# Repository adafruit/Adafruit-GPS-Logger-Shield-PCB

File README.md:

## Adafruit GPS Logger Shield PCB
<a href="http://www.adafruit.com/products/1272"><br/>
Click here to purchase one from the Adafruit shop</a>

Better than ever, our Adafruit assembled GPS shield comes with an Ultimate GPS module. This GPS shield works great with either Adafruit Metro, Arduino UNO or Leonardo and is designed to log data to an SD card. Or you can leave the SD card out and use the GPS for a geocaching project, or maybe a music player that changes tunes depending on where you are in the city.
 
- -165 dBm sensitivity, 10 Hz updates, 66 channels
- Low power module - only 20mA current draw, half of most GPS's
- Assembled & tested shield for Arduino Uno/Duemilanove/Diecimila/Leonardo (not for use with Mega/ADK/Due)
- MicroSD card slot for datalogging onto a removable card
- RTC battery included, for up to 7 years backup
- Built-in datalogging to flash
- PPS output on fix
- Internal patch antenna + u.FL connector for external active antenna
- Power, Pin #13 and Fix status LED
- Big prototyping area

PCB files for Adafruit GPS Logger Shield. The format is EagleCAD schematic and board layout
- https://www.adafruit.com/products/1272

### License

Adafruit invests time and resources providing this open source design, please support Adafruit and open-source hardware by purchasing products from [Adafruit](https://www.adafruit.com)!

All text above must be included in any redistribution

Designed by Limor Fried/Ladyada for Adafruit Industries.
Creative Commons Attribution/Share-Alike, all text above must be included in any redistribution. 
See license.txt for additional information.

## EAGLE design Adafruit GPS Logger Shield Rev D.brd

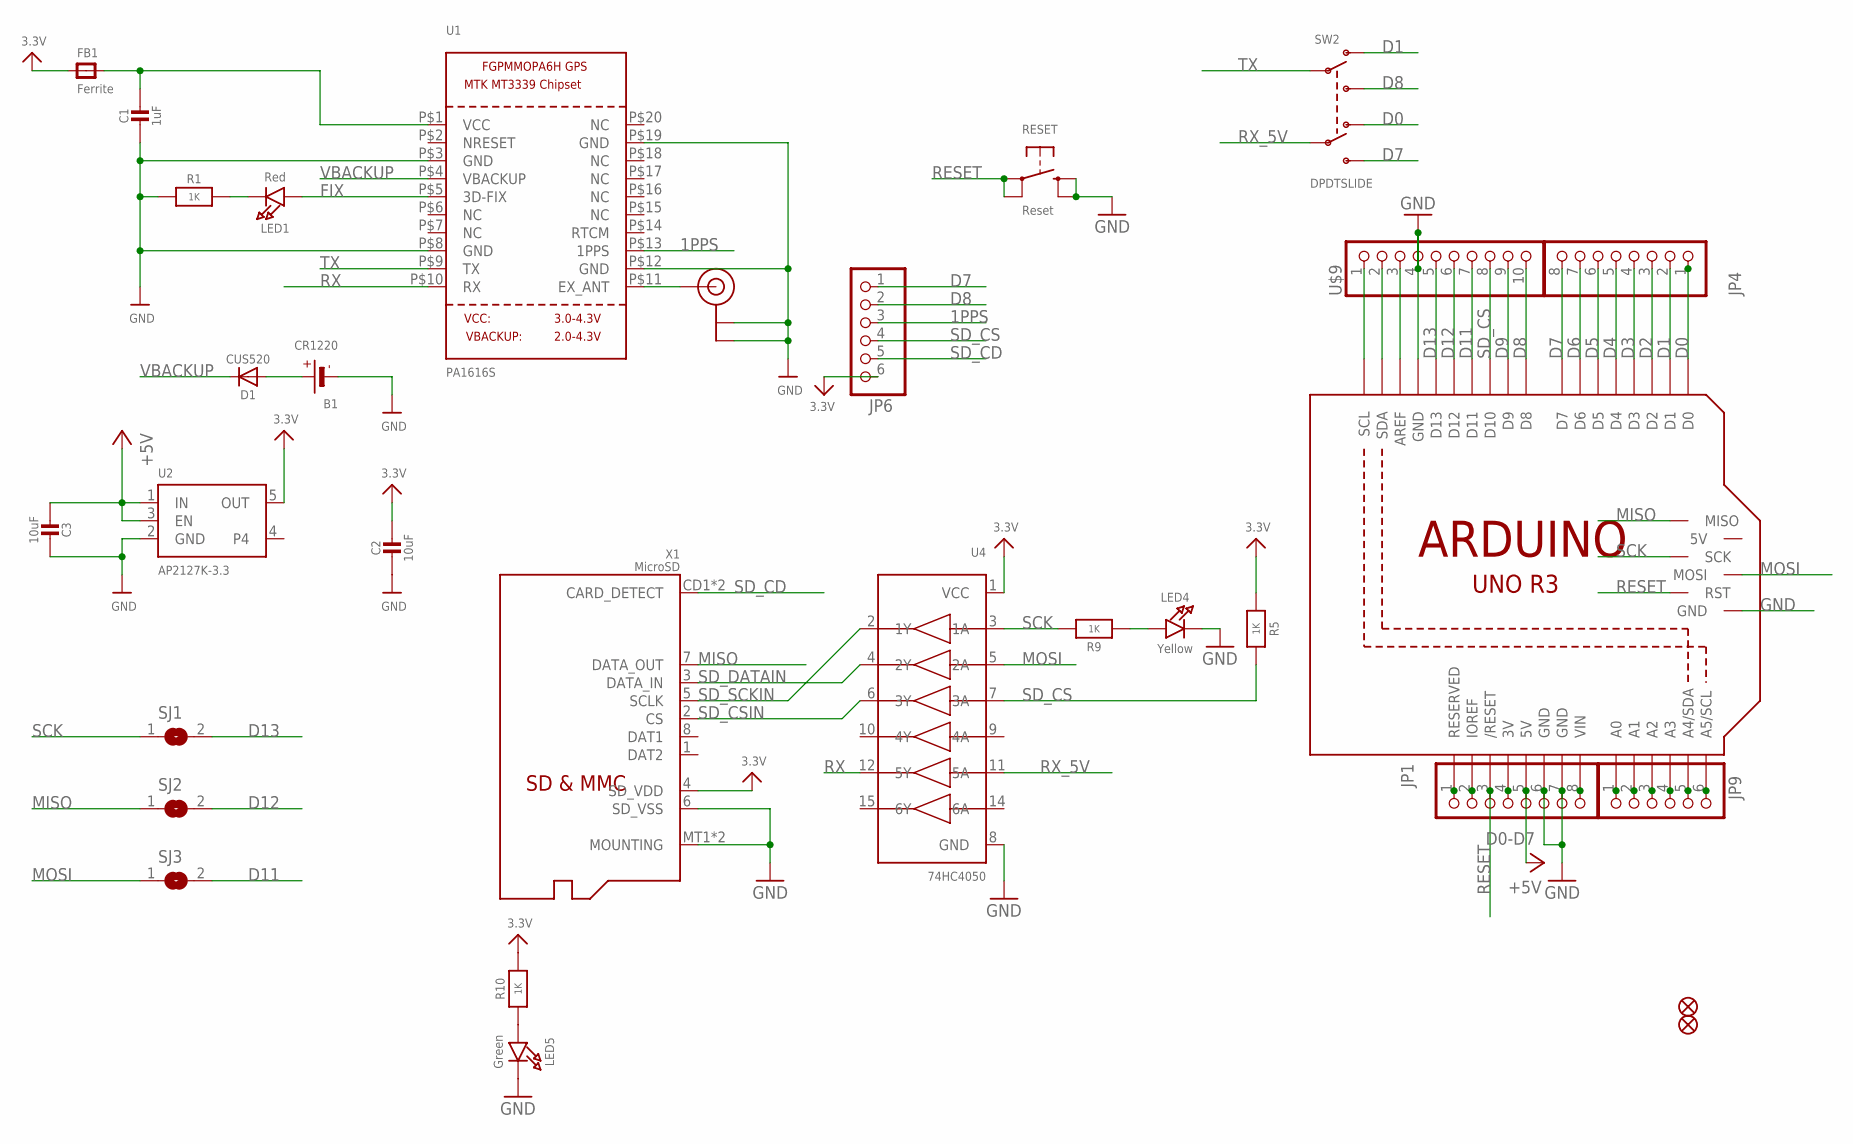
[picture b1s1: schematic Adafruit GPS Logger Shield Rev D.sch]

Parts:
B1: CR1220
C1: 1uF; 0805-NO
C2, C3: 10uF; 0805-NO
D1: CUS520; SOD-323
FB1: Ferrite; 0805
FID1, FID2: FIDUCIAL_1MM
JP1: D0-D7; 1X08-BIG
JP4: PINHD-1X8BIG; 1X08-BIG
JP6, JP9: PINHD-1X6B; 1X06-BIG
LED1: Red; CHIPLED_0805_NOOUTLINE
LED4: Yellow; CHIPLED_0805_NOOUTLINE
LED5: Green; CHIPLED_0805_NOOUTLINE
M1: ARDUINO_R3_ICSP; ARDUINOR3_ICSP
R1, R5, R9, R10: 1K; 0805-NO
RESET: Reset; 6MMX6MM_TACTILE_SMT
SJ1, SJ2, SJ3: SOLDERJUMPER; SOLDERJUMPER_ARROW_NOPASTE
SW2: DPDTSLIDE; EG1390
U1: PA1616S; FGPMMOPA6H
U2: AP2127K-3.3; SOT23-5
U4: 74HC4050; SOIC16
U$9: PINHD-1X10; 1X10-BIG
X1: MicroSD; MICROSD
X2: u.FL; U.FL

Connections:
1PPS: JP6.3, U1.P$13 (1PPS)
3.3V: C2.1, FB1.1, JP6.6, R5.1, R10.2, U2.5 (OUT), U4.1 (VCC), X1.4 (SD_VDD)
3V: JP1.4, M1.3V
+5V: C3.1, JP1.5, M1.5V, U2.1 (IN), U2.3 (EN)
A0: JP9.1, M1.A0
A1: JP9.2, M1.A1
A2: JP9.3, M1.A2
A3: JP9.4, M1.A3
A4: JP9.5, M1.A4 (A4/SDA)
A5: JP9.6, M1.A5 (A5/SCL)
AREF: M1.AREF, U$9.3
D0: JP4.1, M1.D0, SW2.O2
D1: JP4.2, M1.D1, SW2.O1
D2: JP4.3, M1.D2
D3: JP4.4, M1.D3
D4: JP4.5, M1.D4
D5: JP4.6, M1.D5
D6: JP4.7, M1.D6
D7: JP4.8, JP6.1, M1.D7, SW2.S2
D8: JP6.2, M1.D8, SW2.S1, U$9.10
D9: M1.D9, U$9.9
D11: M1.D11, SJ3.2, U$9.7
D12: M1.D12, SJ2.2, U$9.6
D13: M1.D13, SJ1.2, U$9.5
FIX: LED1.A, U1.P$5 (3D-FIX)
GND: B1.-, C1.2, C2.2, C3.2, JP1.6, JP1.7, LED4.C, LED5.C, M1.GND, M1.GND@1 (GND), M1.GND@2 (GND), M1.GND@3 (GND), R1.1, RESET.B (S), RESET.B' (S1), U1.P$3 (GND), U1.P$8 (GND), U1.P$12 (GND), U1.P$19 (GND), U2.2 (GND), U4.8 (GND), U$9.4, X1.6 (SD_VSS), X1.MT1 (MOUNTING), X1.MT2 (MOUNTING), X2.1 (GND), X2.2 (GND)
IOREF: JP1.2, M1.IOREF
MISO: M1.MISO, SJ2.1, X1.7 (DATA_OUT)
MOSI: M1.MOSI, SJ3.1, U4.5 (2A)
unnamed: C1.1, FB1.2, U1.P$1 (VCC)
unnamed: LED1.C, R1.2
unnamed: B1.+$1 (+), B1.+$2 (+), D1.A
unnamed: U1.P$11 (EX_ANT), X2.3 (SIGNAL)
unnamed: LED4.A, R9.1
unnamed: LED5.A, R10.1
NC: JP1.1, M1.RESERVED
RESET: JP1.3, M1.RESET (/RESET), M1.RESET_ICSP (RST), RESET.A, RESET.A' (P1)
RX: U1.P$10 (RX), U4.12 (5Y)
RX_5V: SW2.P2, U4.11 (5A)
SCK: M1.SCK, R9.2, SJ1.1, U4.3 (1A)
SCL: M1.SCL, U$9.1
SDA: M1.SDA, U$9.2
SD_CD: JP6.5, X1.CD1 (CARD_DETECT), X1.CD2 (CARD_DETECT)
SD_CS: JP6.4, M1.D10, R5.2, U4.7 (3A), U$9.8
SD_CSIN: U4.6 (3Y), X1.2 (CS)
SD_DATAIN: U4.4 (2Y), X1.3 (DATA_IN)
SD_SCKIN: U4.2 (1Y), X1.5 (SCLK)
TX: SW2.P1, U1.P$9 (TX)
VBACKUP: D1.C, U1.P$4 (VBACKUP)
VIN: JP1.8, M1.VIN

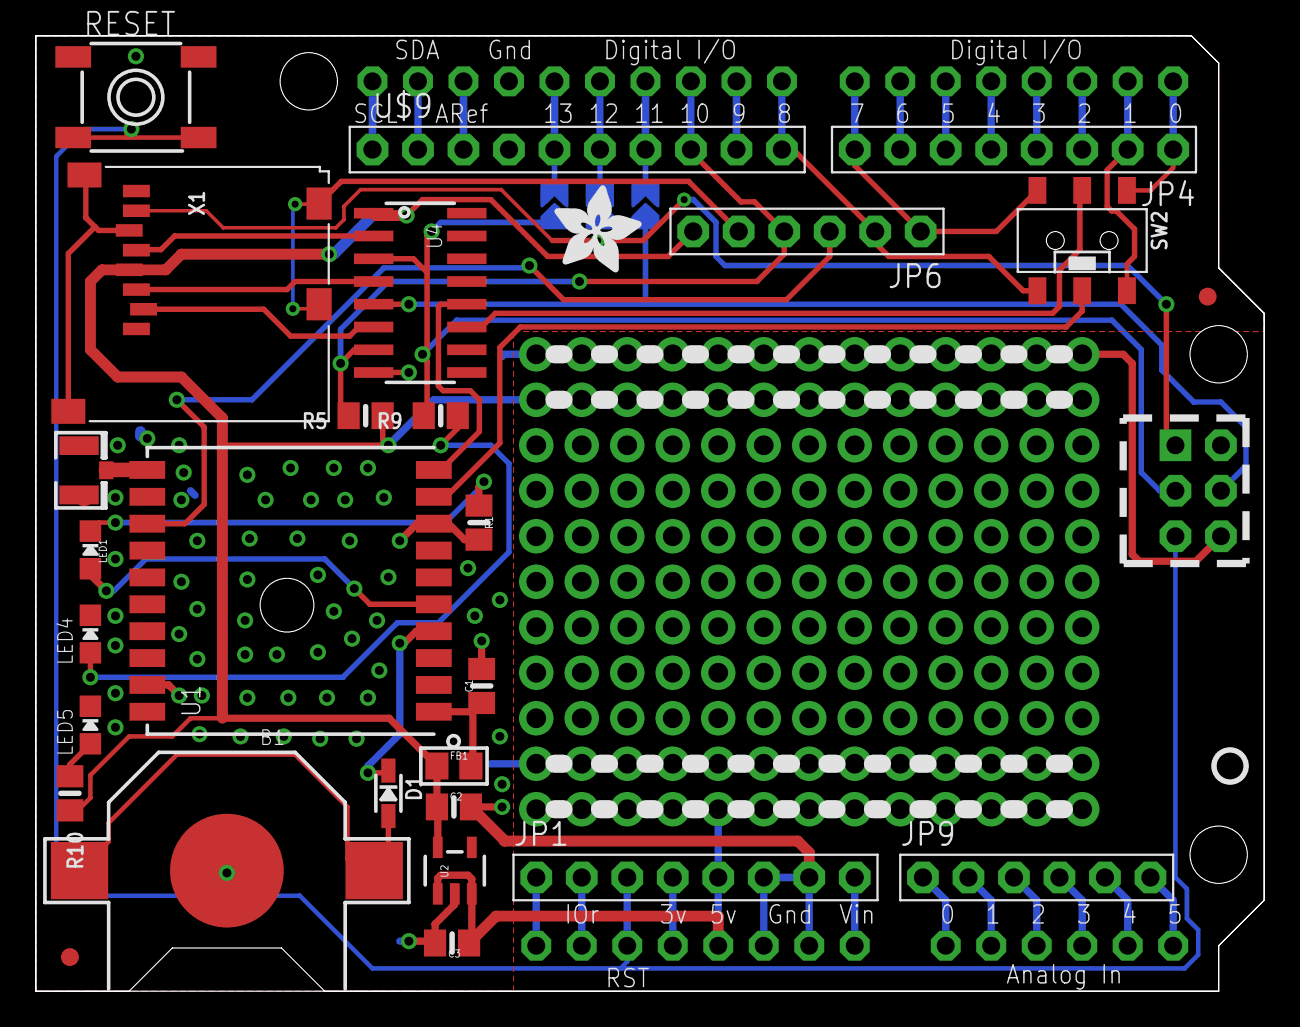
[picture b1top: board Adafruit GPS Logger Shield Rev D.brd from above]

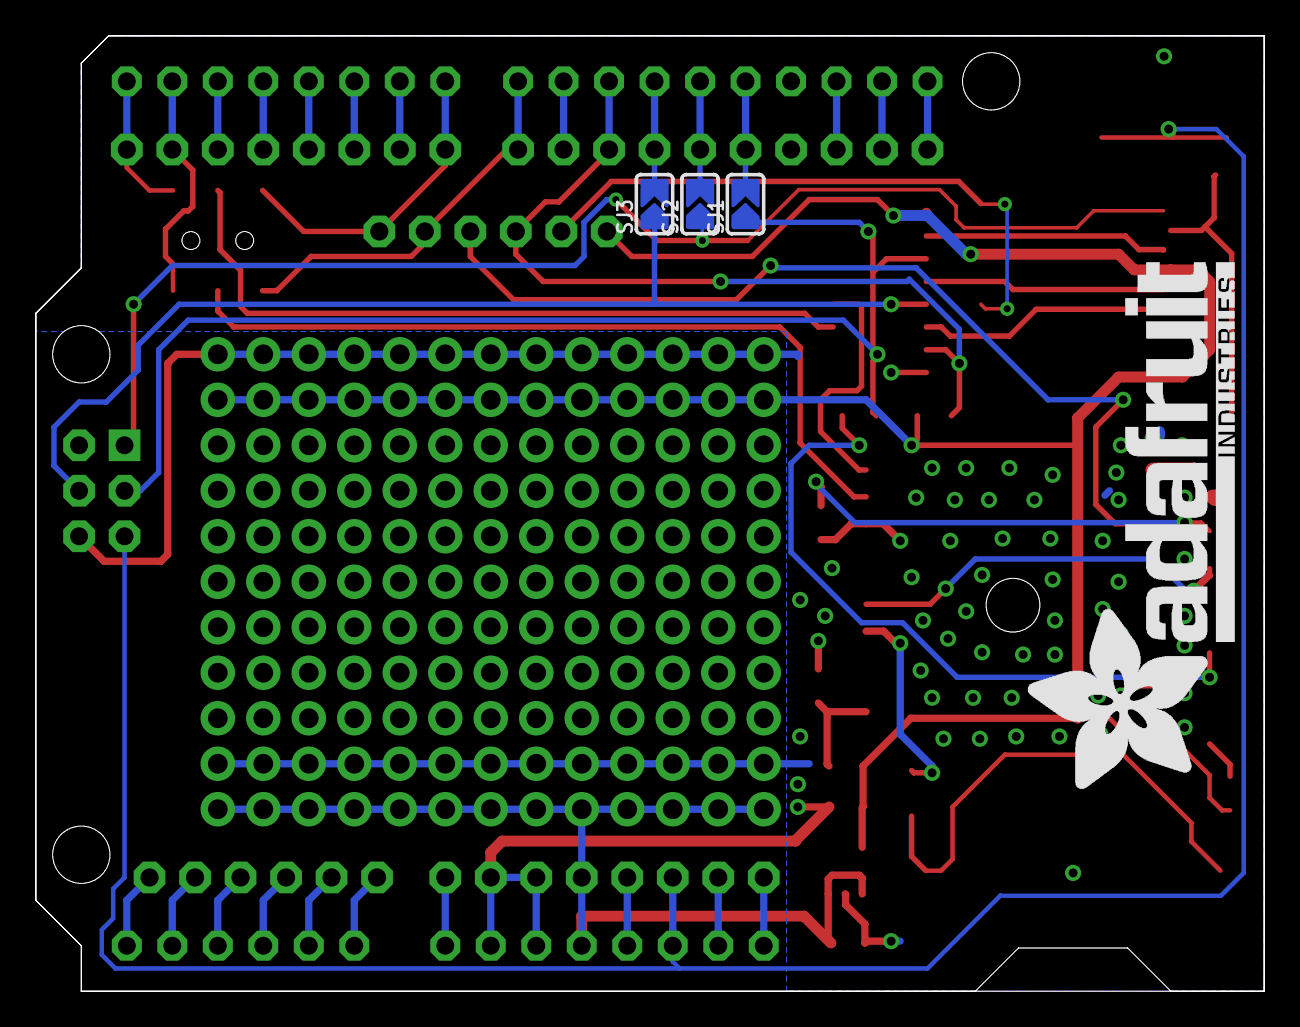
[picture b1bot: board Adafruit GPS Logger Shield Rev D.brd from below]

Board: 2 copper layers, 68.6 x 53.3 mm, 59 parts (7 on the bottom side), 50 nets.

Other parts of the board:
PLABEL0: PLABEL0
PLABEL1: PLABEL1
PLABEL2: PLABEL2
PLABEL3: PLABEL3
PLABEL4: PLABEL4
PLABEL5: PLABEL5
PLABEL6: PLABEL6
PLABEL7: PLABEL7
PLABEL8: PLABEL8
PLABEL9: PLABEL9
PLABEL10: PLABEL10
PLABEL11: PLABEL11
PLABEL12: PLABEL12
PLABEL13: PLABEL13
PLABEL14: PLABEL14
PLABEL15: PLABEL15
PLABEL16: PLABEL16
PLABEL17: PLABEL17
PLABEL18: PLABEL18
PLABEL19: PLABEL19
PLABEL20: PLABEL20
PLABEL21: PLABEL21
PLABEL22: PLABEL22
PLABEL23: PLABEL23
PLABEL24: PLABEL24
U$13: ADAFRUIT_5MM
U$15: ADAFRUIT_TEXT_30MM
U$16: PCBFEAT-REV-040

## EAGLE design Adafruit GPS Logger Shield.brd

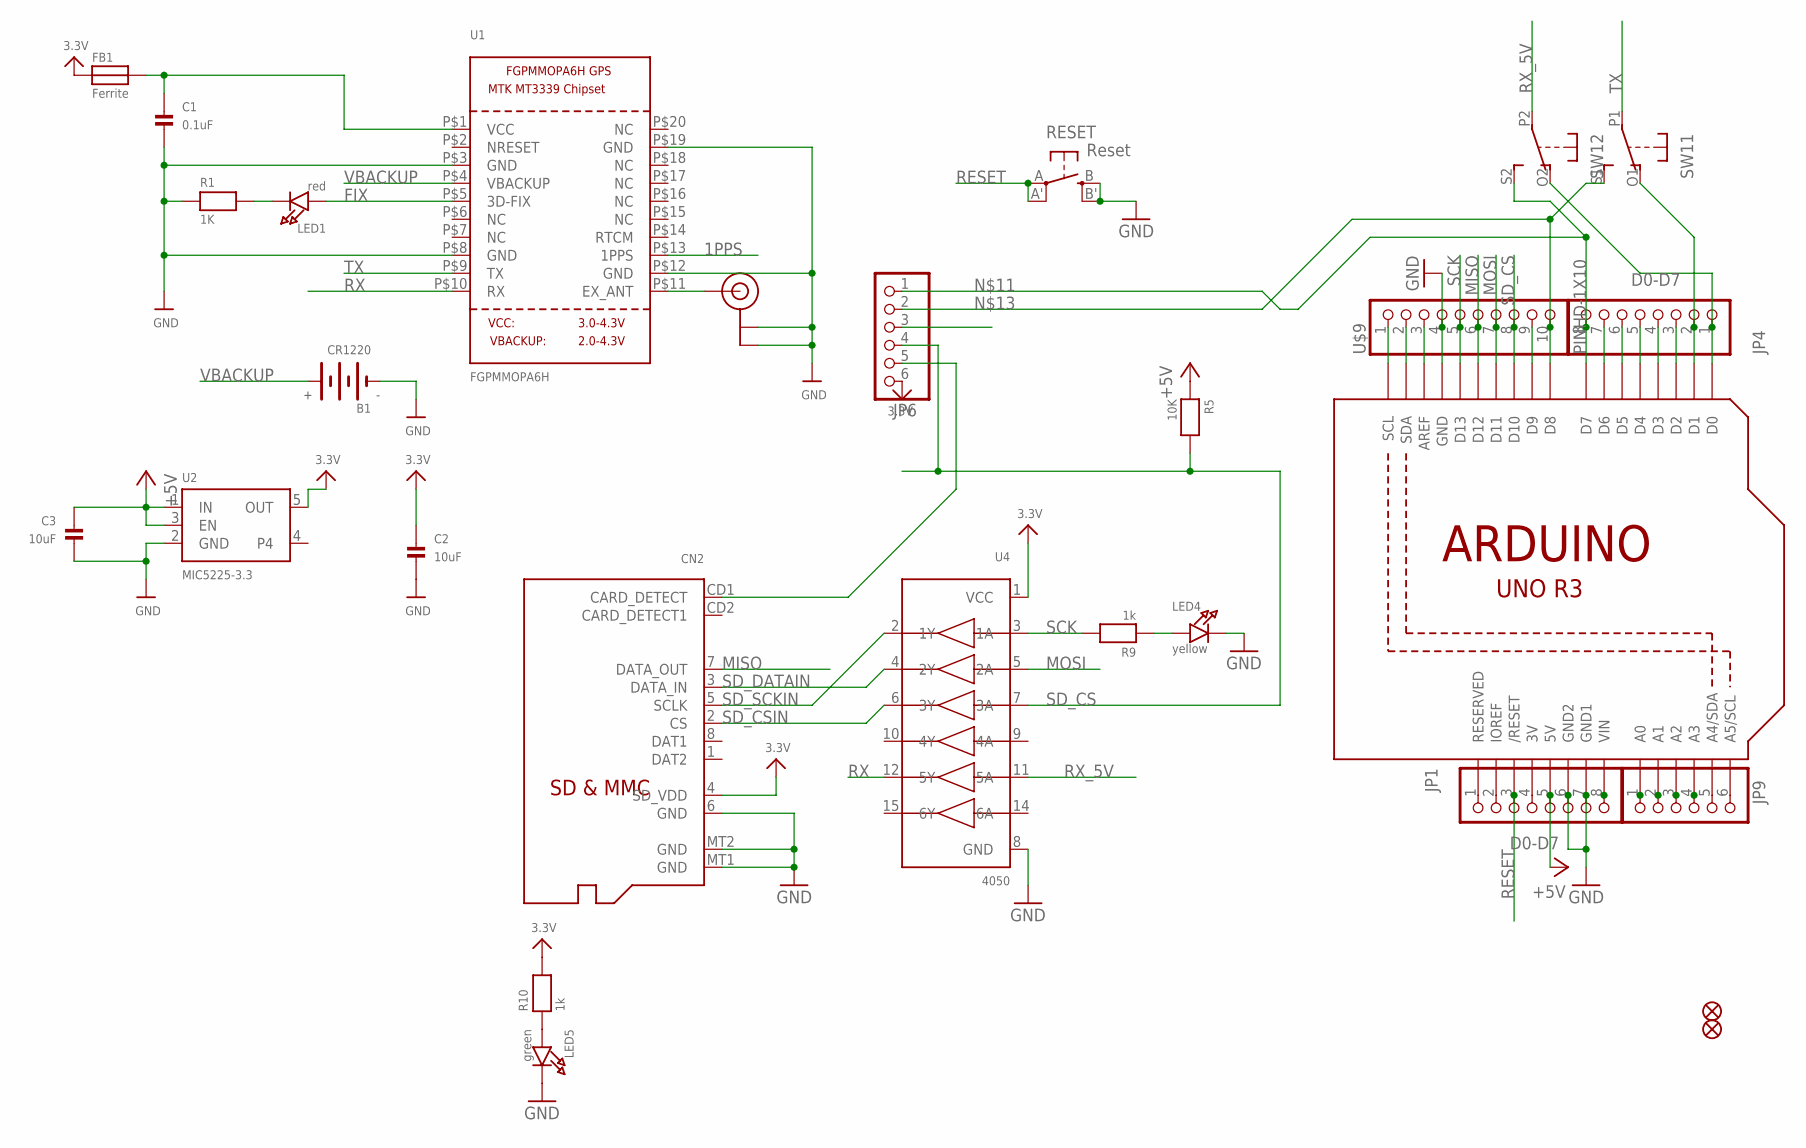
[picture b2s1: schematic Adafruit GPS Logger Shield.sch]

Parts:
B1: CR1220
C1: 0.1uF; 0805@1
C2, C3: 10uF; 0805@1
CN2: MICROSD
FB1: Ferrite; 0805@1
FID1, FID2: FIDUCIAL""; FIDUCIAL_1MM
JP1, JP4: D0-D7; 1X08-BIG
JP6, JP9: PINHD-1X6B; 1X06-BIG
LED1: red; CHIPLED_0805
LED4: yellow; CHIPLED_0805
LED5: green; CHIPLED_0805
R1: 1K; 0805
R5: 10K; 0805
R9, R10: 1k; 0805
RESET: Reset; EVQ-Q2
SW1: DPDT-EG1390; EG1390
U1: FGPMMOPA6H
U2: MIC5225-3.3; SOT23-5
U3: ARDUINOR3-DIMENSION; ARDUINOR3
U4: 4050; SOIC16
U$9: PINHD-1X10; 1X10-BIG
U$20: U.FL

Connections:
1PPS: JP6.3, U1.P$13 (1PPS)
3.3V: C2.1, CN2.4 (SD_VDD), FB1.1, JP6.6, R10.2, U2.5 (OUT), U4.1 (VCC)
+5V: C3.1, JP1.5, R5.1, U2.1 (IN), U2.3 (EN), U3.5V
FIX: LED1.A, U1.P$5 (3D-FIX)
GND: B1.-, C1.2, C2.2, C3.2, CN2.6 (GND), CN2.MT1 (GND), CN2.MT2 (GND), JP1.6, JP1.7, LED4.C, LED5.C, R1.1, RESET.B (S), RESET.B' (S1), U1.P$3 (GND), U1.P$8 (GND), U1.P$12 (GND), U1.P$19 (GND), U2.2 (GND), U3.GND, U3.GND1, U3.GND2, U4.8 (GND), U$9.4, U$20.P$1 (GND), U$20.P$2 (GND)
MISO: CN2.7 (DATA_OUT), U3.D12, U$9.6
MOSI: U3.D11, U4.5 (2A), U$9.7
unnamed: C1.1, FB1.2, U1.P$1 (VCC)
unnamed: LED1.C, R1.2
unnamed: JP1.1, U3.RESERVED
unnamed: U1.P$11 (EX_ANT), U$20.P$3 (SIGNAL)
unnamed: JP1.2, U3.IOREF
unnamed: JP1.4, U3.3V
unnamed: U3.SCL, U$9.1
unnamed: LED4.A, R9.1
unnamed: JP9.6, U3.A5 (A5/SCL)
unnamed: JP9.5, U3.A4 (A4/SDA)
unnamed: JP4.8, JP6.1, SW1.S2 (S), U3.D7
unnamed: U3.SDA, U$9.2
unnamed: JP6.2, SW1.S1 (S), U3.D8, U$9.10
unnamed: JP4.2, SW1.O1 (O), U3.D1
unnamed: JP1.8, U3.VIN
unnamed: JP4.3, U3.D2
unnamed: JP4.4, U3.D3
unnamed: JP4.5, U3.D4
unnamed: JP4.6, U3.D5
unnamed: JP4.7, U3.D6
unnamed: U3.AREF, U$9.3
unnamed: U3.D9, U$9.9
unnamed: LED5.A, R10.1
unnamed: JP9.1, U3.A0
unnamed: JP9.2, U3.A1
unnamed: JP9.3, U3.A2
unnamed: JP9.4, U3.A3
unnamed: JP4.1, SW1.O2 (O), U3.D0
RESET: JP1.3, RESET.A, RESET.A' (P1), U3.RESET (/RESET)
RX: U1.P$10 (RX), U4.12 (5Y)
RX_5V: SW1.P2, U4.11 (5A)
SCK: R9.2, U3.D13, U4.3 (1A), U$9.5
SD_CD: CN2.CD1 (CARD_DETECT), JP6.5
SD_CS: JP6.4, R5.2, U3.D10, U4.7 (3A), U$9.8
SD_CSIN: CN2.2 (CS), U4.6 (3Y)
SD_DATAIN: CN2.3 (DATA_IN), U4.4 (2Y)
SD_SCKIN: CN2.5 (SCLK), U4.2 (1Y)
TX: SW1.P1, U1.P$9 (TX)
VBACKUP: B1.+$1 (+), U1.P$4 (VBACKUP)

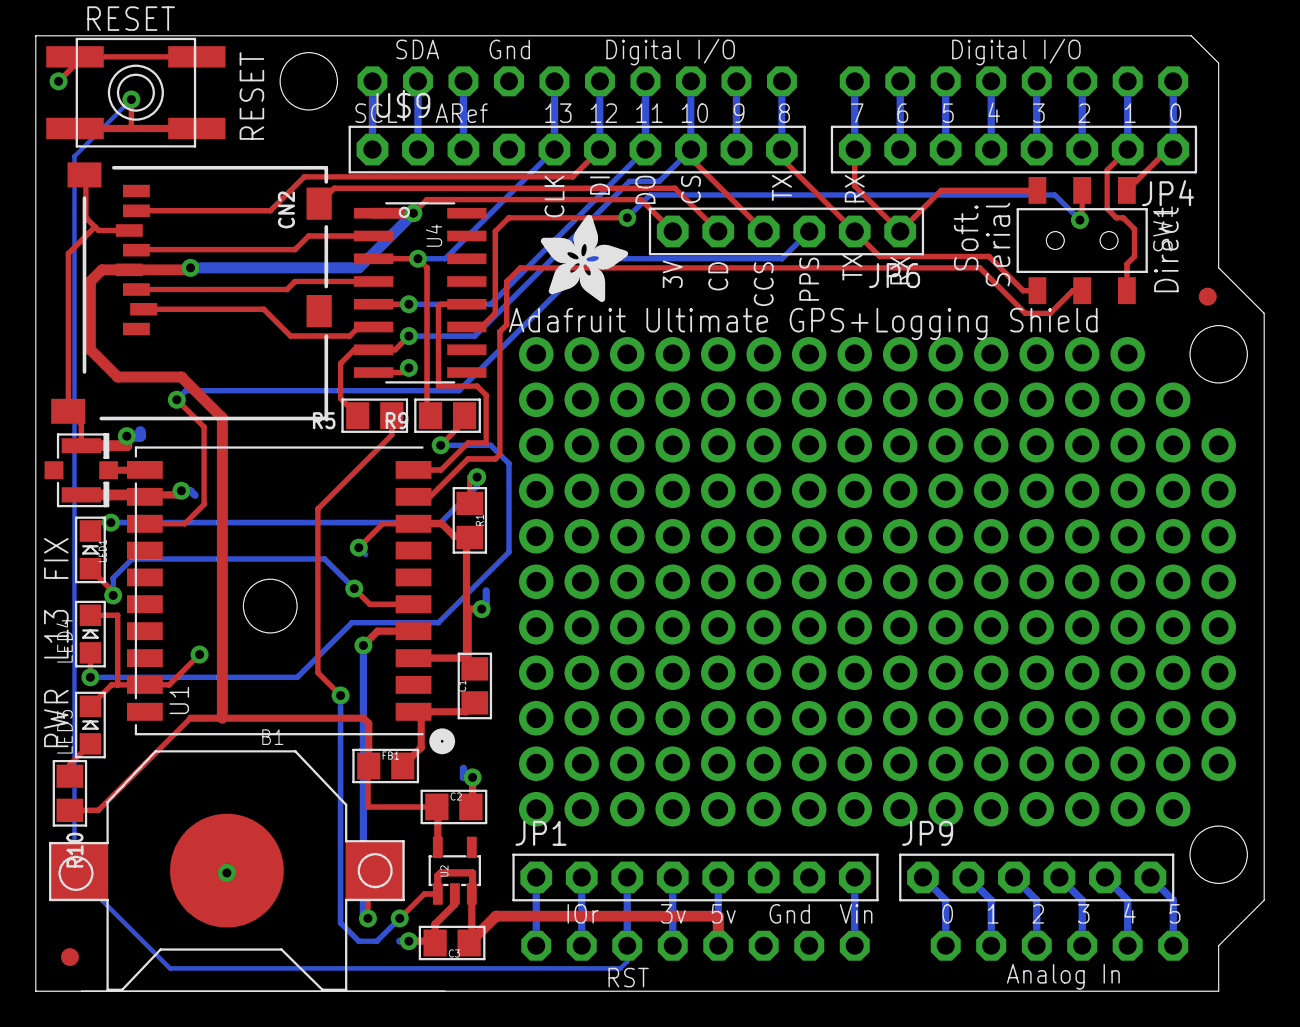
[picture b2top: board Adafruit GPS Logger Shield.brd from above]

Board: 2 copper layers, 68.6 x 53.3 mm, 29 parts (1 on the bottom side), 46 nets.

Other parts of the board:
U$13: ADAFRUIT_5MM
U$15: ADAFRUIT_TEXT_30MM

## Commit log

2016-03-10 init
2023-10-06 adding rev D
